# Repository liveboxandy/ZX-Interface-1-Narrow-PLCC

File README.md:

# ZX-Interface-1-Narrow-PLCC
Sinclair ZX Interface 1 recreated using a standard edge connector along with SMD components where possible along with a PLCC ROM. This design is narrower but longer so does not foul the Tape In/Out sockets but is now too long to be a prototype PCB with JLCPCB.

The schematic available from the Service Guide was redrawn in Kicad and used to create the PCB and to verify that the routing was correct and that no components were missed.

This is the result of that exercise.

Sometimes Kicad complains that there is an issue with the edge.cuts file. Running DRC will show what it doesn't like and it's easy to fix so that the board outline is a closed shape. Currently the pcb is just small enough for JLCPCB to treat it as a prototype for lower pricing.

The file bom/ibom.html is an interactive BOM that will show component position as well as routing in a web browser.

Have fun.

Comments - Good Bad or totally indifferent on https://www.facebook.com/groups/zxspa/

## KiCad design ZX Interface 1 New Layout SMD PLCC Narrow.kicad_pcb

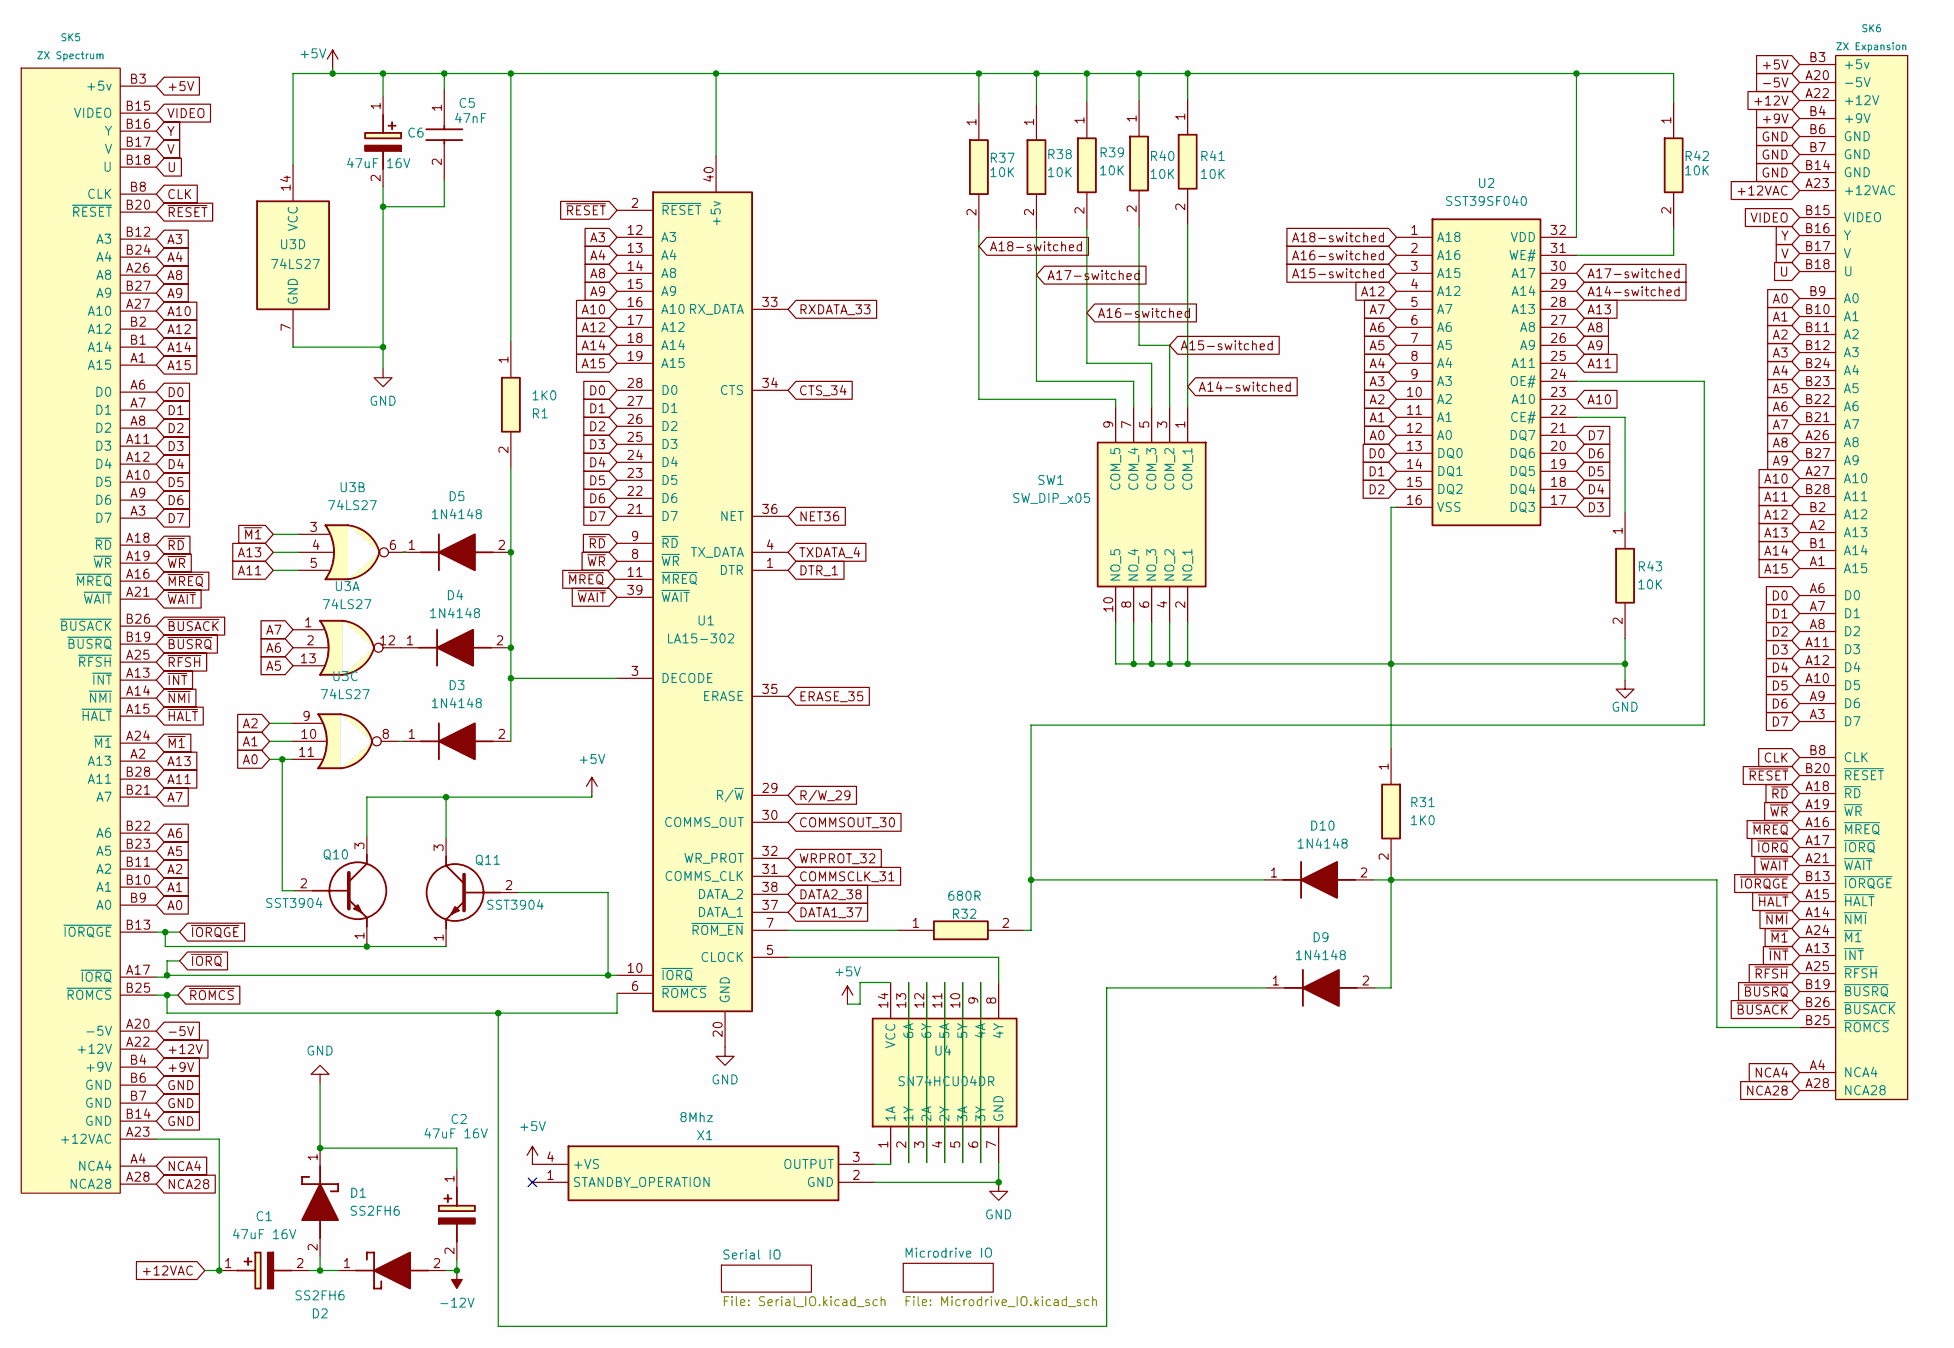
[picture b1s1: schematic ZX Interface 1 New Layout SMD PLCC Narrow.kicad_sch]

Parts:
C1, C2, C6: 47uF 16V; CAPPM7343X310N; Mouser Part Number 74-293D476X9016D2TE3
C5: 47nF; C1206; Mouser Part Number 80-C1206C473K5R
D1, D2: SS2FH6; SODFL3718X108N; Mouser Part Number 78-SS2FH6-M3H
D3, D4, D5, D9, D10: 1N4148; SODFL2512X90N; Mouser Part Number 512-1N4148WS
Q10, Q11: SST3904; SOT95P240X120-3N; Mouser Part Number 755-SST3904HZGT116
R1, R31: 1K0; RESC3216X60N; Mouser Part Number 71-CRCW12061K00FKEAC
R32: 680R; RESC3116X65N; Mouser Part Number 279-CRGH1206F680R
R37, R38, R39, R40, R41, R42, R43: 10K; RESC3116X65N; Mouser Part Number 279-CRG1206F10K
SK5: ZX Spectrum; ZX_Spectrum_BUS_Edge_Connector
SK6: ZX Expansion; ZX_Expansion_BUS_Edge_Connector
SW1: SW_DIP_x05; A6FR5104; Mouser Part Number 653-A6FR-5104
U1: LA15-302; DIP-40_W15.24mm
U2: SST39SF040; MC32PLCC; Mouser Part Number 804-39SF0407CPHE
U3: 74LS27; SOIC127P600X175-14N; Mouser Part Number 595-SN74LS27D
U4: SN74HCU04DR; SOIC127P600X175-14N; Mouser Part Number 595-SN74HCU04DR
X1: 8Mhz; 830202129201; Mouser Part Number 449-LFSPXO021292BULK

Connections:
+5V: C5.1, C6.1 (+), Q10.3 (C), Q11.3 (C), R1.1, R37.1, R38.1, R39.1, R40.1, R41.1, R42.1, SK5.B3 (+5v), SK6.B3 (+5v), U1.40 (+5v), U2.32 (VDD), U3.14 (VCC), U4.14 (VCC), X1.4 (+VS); also elsewhere on the board
+9V: SK5.B4 (+9V), SK6.B4 (+9V); also elsewhere on the board
+12V: SK5.A22 (+12V), SK6.A22 (+12V); also elsewhere on the board
+12VAC: C1.1 (+), SK5.A23 (+12VAC), SK6.A23 (+12VAC)
-5V: SK5.A20 (-5V), SK6.A20 (-5V)
-12V: C2.2 (-), D2.2 (A); also elsewhere on the board
A0: Q10.2 (B), SK5.B9 (A0), SK6.B9 (A0), U2.12 (A0), U3.11
A1: SK5.B10 (A1), SK6.B10 (A1), U2.11 (A1), U3.10
A2: SK5.B11 (A2), SK6.B11 (A2), U2.10 (A2), U3.9
A3: SK5.B12 (A3), SK6.B12 (A3), U1.12 (A3), U2.9 (A3)
A4: SK5.B24 (A4), SK6.B24 (A4), U1.13 (A4), U2.8 (A4)
A5: SK5.B23 (A5), SK6.B23 (A5), U2.7 (A5), U3.13
A6: SK5.B22 (A6), SK6.B22 (A6), U2.6 (A6), U3.2
A7: SK5.B21 (A7), SK6.B21 (A7), U2.5 (A7), U3.1
A8: SK5.A26 (A8), SK6.A26 (A8), U1.14 (A8), U2.27 (A8)
A9: SK5.B27 (A9), SK6.B27 (A9), U1.15 (A9), U2.26 (A9)
A10: SK5.A27 (A10), SK6.A27 (A10), U1.16 (A10), U2.23 (A10)
A11: SK5.B28 (A11), SK6.B28 (A11), U2.25 (A11), U3.5
A12: SK5.B2 (A12), SK6.B2 (A12), U1.17 (A12), U2.4 (A12)
A13: SK5.A2 (A13), SK6.A2 (A13), U2.28 (A13), U3.4
A14: SK5.B1 (A14), SK6.B1 (A14), U1.18 (A14)
A14-switched: R41.2, SW1.1 (COM_1), U2.29 (A14)
A15: SK5.A1 (A15), SK6.A1 (A15), U1.19 (A15)
A15-switched: R40.2, SW1.3 (COM_2), U2.3 (A15)
A16-switched: R39.2, SW1.5 (COM_3), U2.2 (A16)
A17-switched: R38.2, SW1.7 (COM_4), U2.30 (A17)
A18-switched: R37.2, SW1.9 (COM_5), U2.1 (A18)
CLK: SK5.B8 (CLK), SK6.B8 (CLK)
COMMSCLK_31: U1.31 (COMMS_CLK); also elsewhere on the board
COMMSOUT_30: U1.30 (COMMS_OUT); also elsewhere on the board
CTS_34: U1.34 (CTS); also elsewhere on the board
D0: SK5.A6 (D0), SK6.A6 (D0), U1.28 (D0), U2.13 (DQ0)
D1: SK5.A7 (D1), SK6.A7 (D1), U1.27 (D1), U2.14 (DQ1)
D2: SK5.A8 (D2), SK6.A8 (D2), U1.26 (D2), U2.15 (DQ2)
D3: SK5.A11 (D3), SK6.A11 (D3), U1.25 (D3), U2.17 (DQ3)
D4: SK5.A12 (D4), SK6.A12 (D4), U1.24 (D4), U2.18 (DQ4)
D5: SK5.A10 (D5), SK6.A10 (D5), U1.23 (D5), U2.19 (DQ5)
D6: SK5.A9 (D6), SK6.A9 (D6), U1.22 (D6), U2.20 (DQ6)
D7: SK5.A3 (D7), SK6.A3 (D7), U1.21 (D7), U2.21 (DQ7)
DATA1_37: U1.37 (DATA_1); also elsewhere on the board
DATA2_38: U1.38 (DATA_2); also elsewhere on the board
DTR_1: U1.1 (DTR); also elsewhere on the board
ERASE_35: U1.35 (ERASE); also elsewhere on the board
GND: C2.1 (+), C5.2, C6.2 (-), D1.1 (K), R31.1, R43.2, SK5.B6 (GND), SK5.B7 (GND), SK5.B14 (GND), SK6.B6 (GND), SK6.B7 (GND), SK6.B14 (GND), SW1.2 (NO_1), SW1.4 (NO_2), SW1.6 (NO_3), SW1.8 (NO_4), SW1.10 (NO_5), U1.20 (GND), U2.16 (VSS), U3.7 (GND), U4.7 (GND), X1.2 (GND); also elsewhere on the board
NCA4: SK5.A4 (NCA4), SK6.A4 (NCA4)
NCA28: SK5.A28 (NCA28), SK6.A28 (NCA28)
NET36: U1.36 (NET); also elsewhere on the board
unnamed: C1.2 (-), D1.2 (A), D2.1 (K)
unnamed: D3.2 (A), D4.2 (A), D5.2 (A), R1.2, U1.3 (DECODE)
unnamed: D3.1 (K), U3.8
unnamed: D4.1 (K), U3.12
unnamed: D5.1 (K), U3.6
unnamed: D9.2 (A), D10.2 (A), R31.2, SK6.B25 (~ROMCS)
unnamed: D10.1 (K), R32.2, U2.24 (OE#)
unnamed: U1.5 (CLOCK), U4.8 (4Y)
unnamed: R32.1, U1.7 (~ROM_EN)
unnamed: R43.1, U2.22 (CE#)
unnamed: R42.2, U2.31 (WE#)
unnamed: U4.1 (1A), X1.3 (OUTPUT)
unnamed: U4.2 (1Y), U4.13 (6A)
unnamed: U4.3 (2A), U4.12 (6Y)
unnamed: U4.4 (2Y), U4.11 (5A)
unnamed: U4.5 (3A), U4.10 (5Y)
unnamed: U4.6 (3Y), U4.9 (4A)
RXDATA_33: U1.33 (RX_DATA); also elsewhere on the board
R/W_29: U1.29 (R/~W); also elsewhere on the board
TXDATA_4: U1.4 (TX_DATA); also elsewhere on the board
U: SK5.B18 (U), SK6.B18 (U)
V: SK5.B17 (V), SK6.B17 (V)
VIDEO: SK5.B15 (VIDEO), SK6.B15 (VIDEO)
WRPROT_32: U1.32 (WR_PROT); also elsewhere on the board
Y: SK5.B16 (Y), SK6.B16 (Y)
~BUSACK: SK5.B26 (~BUSACK), SK6.B26 (~BUSACK)
~BUSRQ: SK5.B19 (~BUSRQ), SK6.B19 (~BUSRQ)
~HALT: SK5.A15 (~HALT), SK6.A15 (~HALT)
~INT: SK5.A13 (~INT), SK6.A13 (~INT)
~IORQGE: Q10.1 (E), Q11.1 (E), SK5.B13 (~IORQGE), SK6.B13 (~IORQGE)
~IORQ: Q11.2 (B), SK5.A17 (~IORQ), SK6.A17 (~IORQ), U1.10 (~IORQ)
~M1: SK5.A24 (~M1), SK6.A24 (~M1), U3.3
~MREQ: SK5.A16 (~MREQ), SK6.A16 (~MREQ), U1.11 (~MREQ)
~NMI: SK5.A14 (~NMI), SK6.A14 (~NMI)
~RD: SK5.A18 (~RD), SK6.A18 (~RD), U1.9 (~RD)
~RESET: SK5.B20 (~RESET), SK6.B20 (~RESET), U1.2 (~RESET)
~RFSH: SK5.A25 (~RFSH), SK6.A25 (~RFSH)
~ROMCS: D9.1 (K), SK5.B25 (~ROMCS), U1.6 (~ROMCS)
~WAIT: SK5.A21 (~WAIT), SK6.A21 (~WAIT), U1.39 (~WAIT)
~WR: SK5.A19 (~WR), SK6.A19 (~WR), U1.8 (~WR)

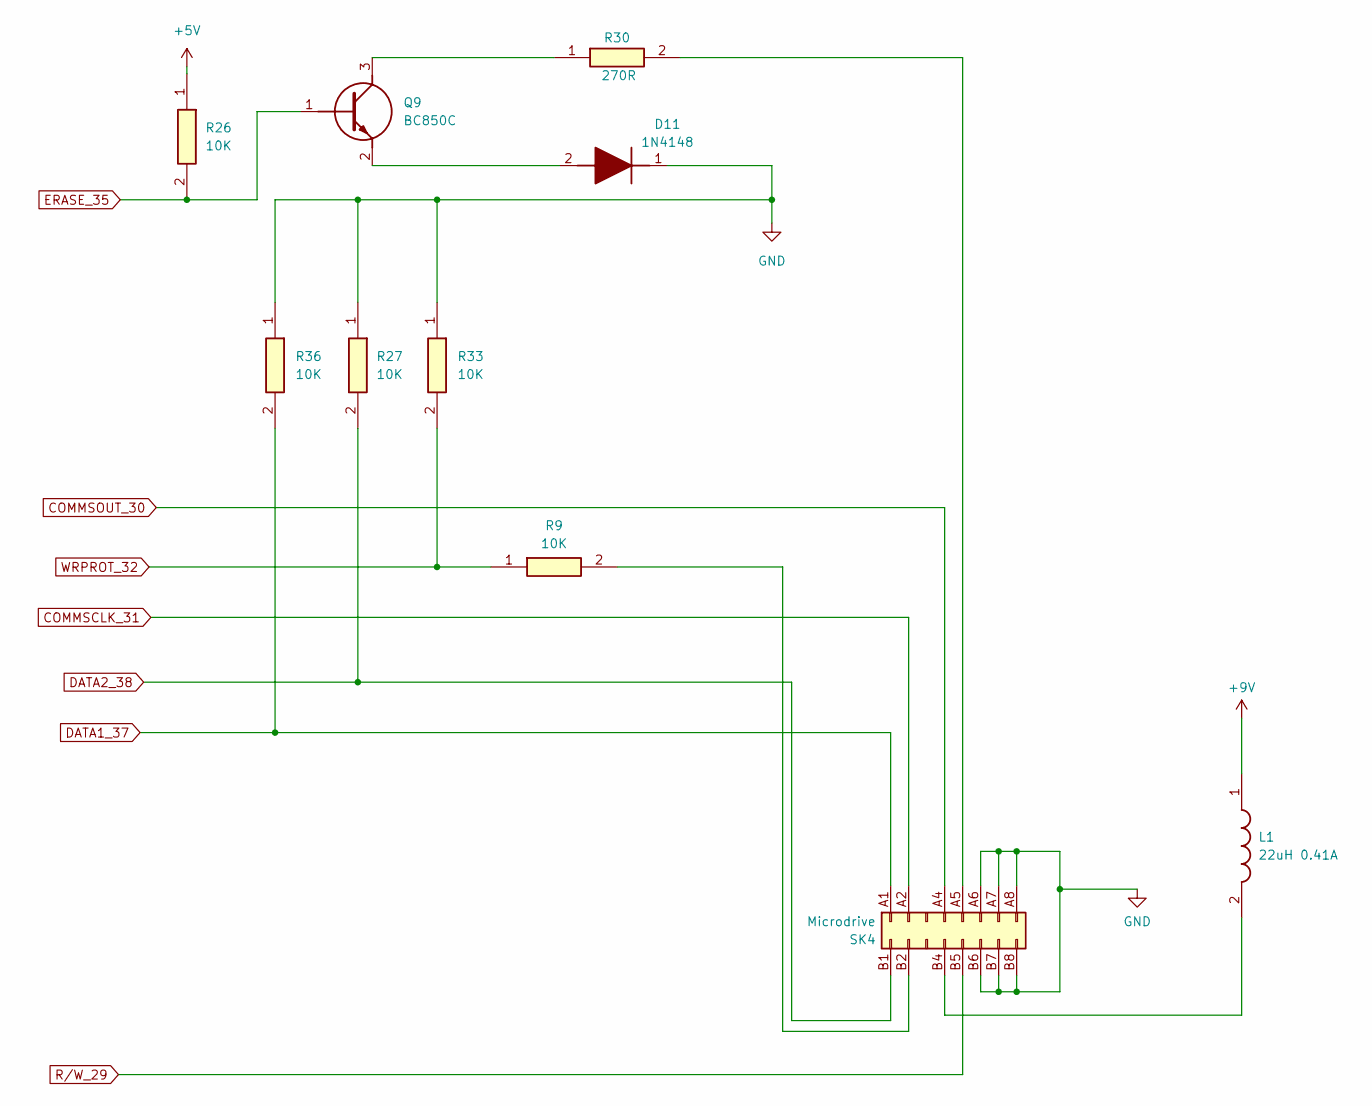
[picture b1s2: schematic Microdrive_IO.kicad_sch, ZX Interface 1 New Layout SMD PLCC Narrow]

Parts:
D11: 1N4148; SODFL2512X90N; Mouser Part Number 512-1N4148WS
L1: 22uH 0.41A; LQH2MCN100K02L; Mouser Part Number 81-LQH2MPN220MGRL
Q9: BC850C; BC850C215; Mouser Part Number 771-BC850C-T/R
R9, R26, R27, R33, R36: 10K; RESC3116X65N; Mouser Part Number 279-CRG1206F10K
R30: 270R; RESC3216X60N; Mouser Part Number 71-CRCW1206-270-E3
SK4: Microdrive; ZX_MD_Edge_Connector

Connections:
+5V: R26.1; also elsewhere on the board
+9V: L1.1; also elsewhere on the board
COMMSCLK_31: SK4.A2; also elsewhere on the board
COMMSOUT_30: SK4.A4; also elsewhere on the board
DATA1_37: R36.2, SK4.A1; also elsewhere on the board
DATA2_38: R27.2, SK4.B1; also elsewhere on the board
ERASE_35: Q9.1 (B), R26.2; also elsewhere on the board
GND: D11.1 (K), R27.1, R33.1, R36.1, SK4.A6, SK4.A7, SK4.A8, SK4.B6, SK4.B7, SK4.B8; also elsewhere on the board
unnamed: D11.2 (A), Q9.2 (E)
unnamed: Q9.3 (C), R30.1
unnamed: R30.2, SK4.A5
unnamed: R9.2, SK4.B2
unnamed: L1.2, SK4.B4
R/W_29: SK4.B5; also elsewhere on the board
WRPROT_32: R9.1, R33.2; also elsewhere on the board

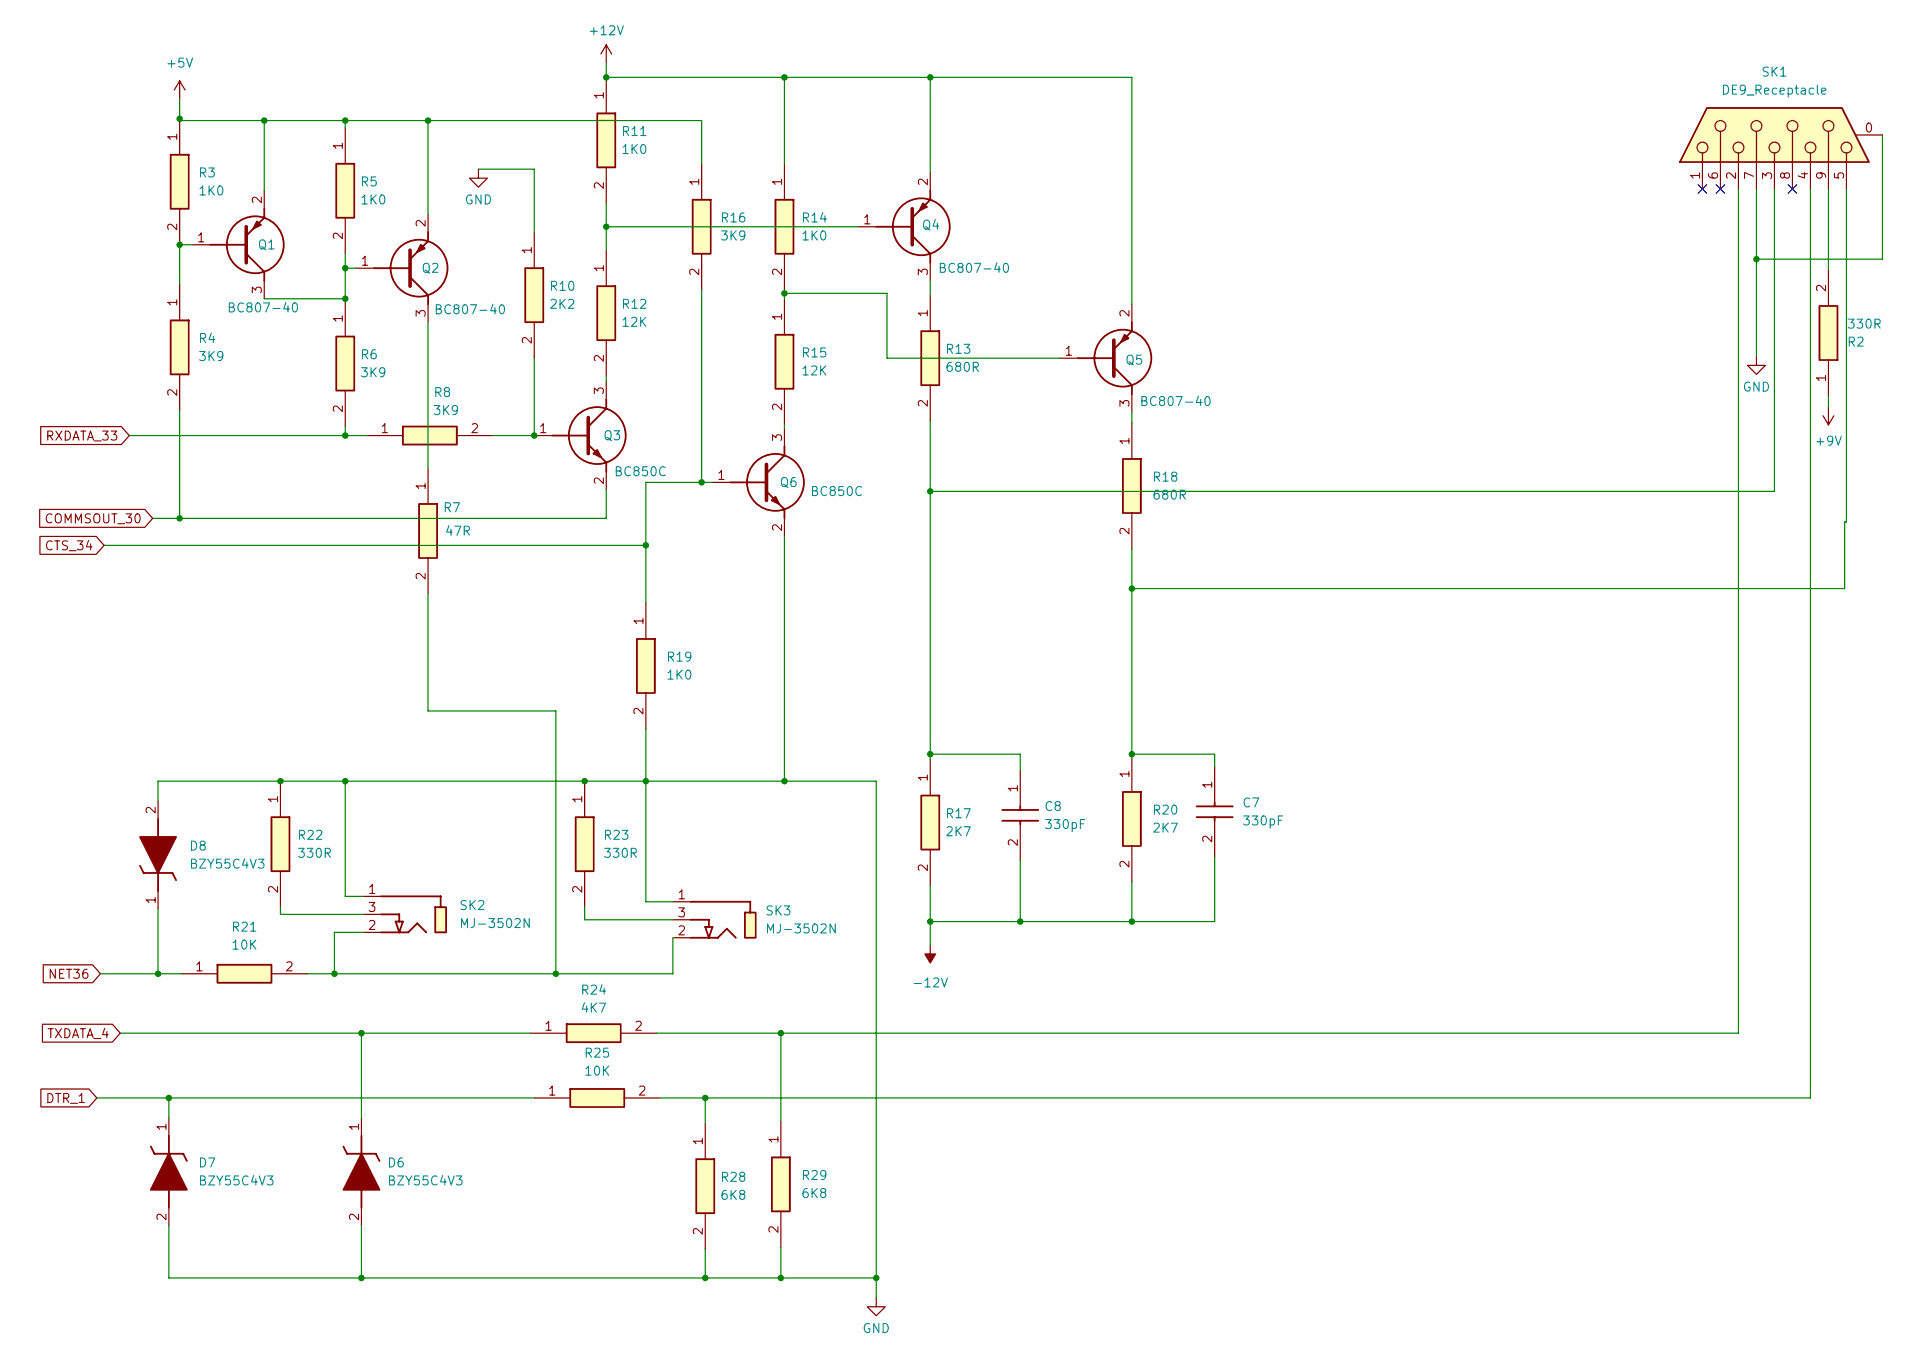
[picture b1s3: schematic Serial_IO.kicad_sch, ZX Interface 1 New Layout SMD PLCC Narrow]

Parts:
C7, C8: 330pF; CAPC3317X75N; Mouser Part Number 810-C3216C0G2J331J
D6, D7, D8: BZY55C4V3; DIOC2012X85N; Manufacturer_Part_Number BZY55C4V3 RBG; Mouser Part Number 821-BZY55C4V3RBG
Q1, Q2, Q4, Q5: BC807-40; SOT95P230X110-3N; Mouser Part Number 771-BC807-40-T/R
Q3, Q6: BC850C; BC850C215; Mouser Part Number 771-BC850C-T/R
R2, R22, R23: 330R; RESC3116X65N; Mouser Part Number 279-CRGH1206F330R
R3, R5, R11, R14, R19: 1K0; RESC3216X60N; Mouser Part Number 71-CRCW12061K00FKEAC
R4, R6, R8, R16: 3K9; RESC3216X60N; Mouser Part Number 71-CRCW1206-3.9K-E3
R7: 47R; RCC1206_e3; Mouser Part Number 71-RCC120647R0FKEA
R10: 2K2; RESC3216X60N; Mouser Part Number 71-CRCW1206-2.2K-E3
R12, R15: 12K; RESC3216X60N; Mouser Part Number 71-CRCW120612K4FKEAC
R13, R18: 680R; RESC3116X65N; Mouser Part Number 279-CRGH1206F680R
R17, R20: 2K7; RESC3116X65N; Mouser Part Number 279-CRGH1206F2K7
R21, R25: 10K; RESC3116X65N; Mouser Part Number 279-CRG1206F10K
R24: 4K7; RESC3116X65N; Manufacturer_Part_Number CRGS1206J4K7
R28, R29: 6K8; RESC3116X65N; Mouser Part Number 279-CRG1206F6K8
SK1: DE9_Receptacle; DSUB-9_Female_Horizontal_P2.77x2.84mm_EdgePinOffset4.94mm_H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
SK2, SK3: MJ-3502N; MJ3502N; Mouser Part Number 490-MJ-3502N

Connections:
+5V: Q1.2 (E), Q2.2 (E), R3.1, R5.1, R16.1; also elsewhere on the board
+9V: R2.1; also elsewhere on the board
+12V: Q4.2 (E), Q5.2 (E), R11.1, R14.1; also elsewhere on the board
-12V: C7.2, C8.2, R17.2, R20.2; also elsewhere on the board
COMMSOUT_30: Q3.2 (E), R4.2; also elsewhere on the board
CTS_34: Q6.1 (B), R16.2, R19.1; also elsewhere on the board
DTR_1: D7.1 (K), R25.1; also elsewhere on the board
GND: D6.2 (A), D7.2 (A), D8.2 (A), Q6.2 (E), R10.1, R19.2, R22.1, R23.1, R28.2, R29.2, SK1.0 (PAD), SK1.7, SK2.1, SK3.1; also elsewhere on the board
NET36: D8.1 (K), R21.1; also elsewhere on the board
unnamed: C7.1, R18.2, R20.1, SK1.5
unnamed: C8.1, R13.2, R17.1, SK1.3
unnamed: Q1.1 (B), R3.2, R4.1
unnamed: Q1.3 (C), Q2.1 (B), R5.2, R6.1
unnamed: Q2.3 (C), R7.1
unnamed: Q3.1 (B), R8.2, R10.2
unnamed: Q3.3 (C), R12.2
unnamed: Q4.1 (B), R11.2, R12.1
unnamed: Q4.3 (C), R13.1
unnamed: Q5.1 (B), R14.2, R15.1
unnamed: Q5.3 (C), R18.1
unnamed: Q6.3 (C), R15.2
unnamed: R2.2, SK1.9
unnamed: R7.2, R21.2, SK2.2, SK3.2
unnamed: R22.2, SK2.3
unnamed: R23.2, SK3.3
unnamed: R24.2, R29.1, SK1.2
unnamed: R25.2, R28.1, SK1.4
RXDATA_33: R6.2, R8.1; also elsewhere on the board
TXDATA_4: D6.1 (K), R24.1; also elsewhere on the board

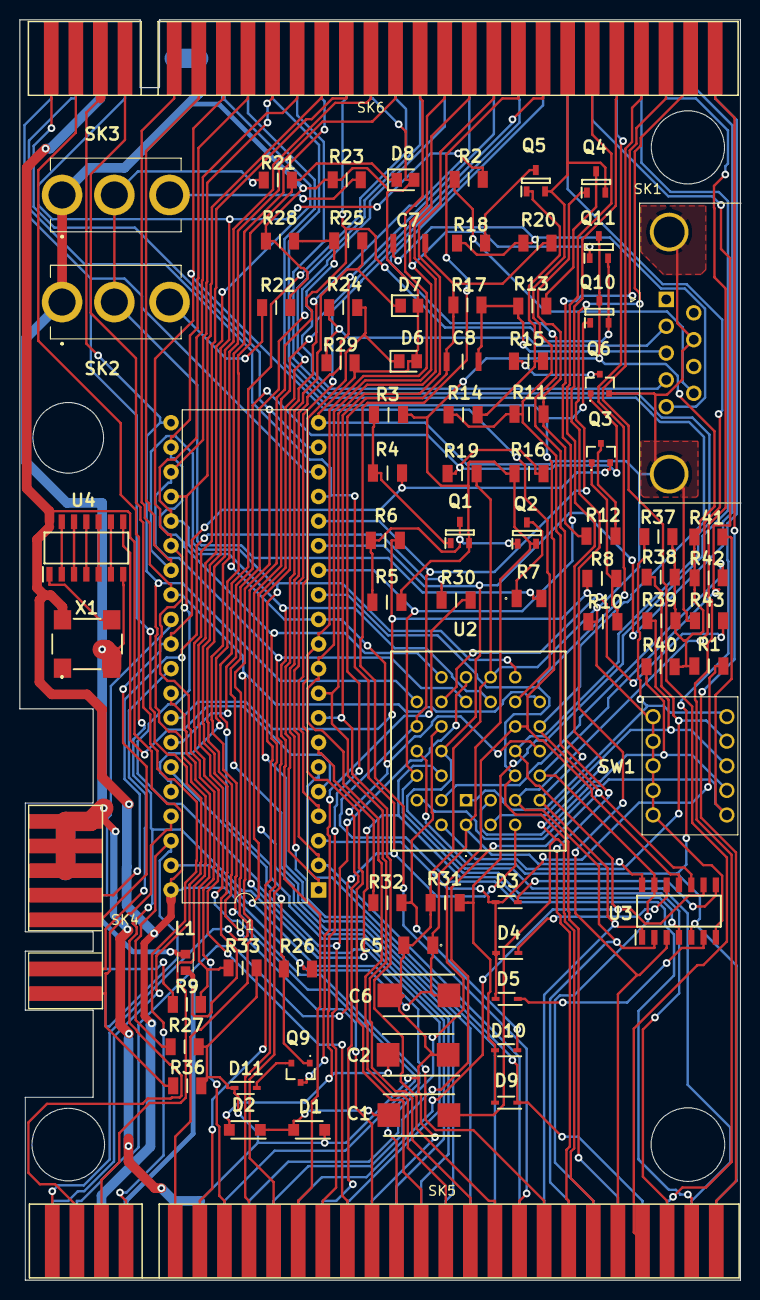
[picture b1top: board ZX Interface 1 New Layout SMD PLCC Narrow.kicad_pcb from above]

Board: 2 copper layers, 74.4 x 130.2 mm, 80 parts (0 on the bottom side), 110 nets.
